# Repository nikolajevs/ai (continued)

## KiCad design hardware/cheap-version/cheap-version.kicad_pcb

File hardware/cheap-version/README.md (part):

# cheap-version — одноразовая плата из того, что есть

Версия **cheap-1** платы GrowBox: те же функции и прошивка, что у PCB_V1 (ревизия 0.22), но детали берутся со склада пользователя, докупается только недостающее. Это отдельный проект, а не ревизия PCB_V1: `../PCB_V1/` не меняется.

**Решения пользователя (03.10.2026):** основа — копия схемы PCB_V1 с заменами; плата 4 слоя, 100×100 мм, стек как у PCB_V1 (1,6 мм, 1 oz снаружи / 0,5 oz внутри); ESP32-WROOM-32E на плате, прошивка и GPIO без изменений; J901 — винтовой клеммник KF301 вместо XT60, защиты от переполюсовки не нужно; L711 — Feryster DTMSS-27/0.047/15-V **на плате стоймя** (корпус будет выше); выходные 10 мкФ 100 В X7S докупаются, как в V1 (4,7 мкФ X7R со склада не берём).

**Решения пользователя (04.10.2026):** CH1 рассчитан на **80 Вт** (R716 0,12 Ом вместо 0,18; LED-панель допускает до 120 Вт, плата её не догружает), драйвер нагревателя — снова **UCC27524ADR** (как в V1) вместо IRS4427S, затем шина +12V и шелкография.

## Состояние

- **Схема готова к проверке** (`cheap-version.kicad_sch` + 6 листов). Её строит `tools/make_cheap1.py` из `../PCB_V1/` (от базовой схемы каждый раз заново). Остальные инструменты: `tools/sch_edit.py` — редактор текста схем, `tools/netdiff.py` — сравнение связности с PCB_V1, `tools/make_footprints.py` — свои футпринты (запуск Python из KiCad), `tools/make_models3d.py` — их 3D-модели (CadQuery), `tools/analyze_led_cheap.py` — расчёт LED-boost. После ручных правок схемы в KiCad `make_cheap1.py` больше не запускать.
- ERC: **0 нарушений**. Связность у всех нетронутых выводов совпадает с PCB_V1 (`netdiff.py`: 0 различий).
- Свои футпринты и упрощённые 3D: `Diodes_PowerDI5`, `L_Feryster_DTMSS-27_V` (`libraries/`). BOM — `BOM_cheap1.csv`, `BUY_cheap1.csv` (см. ниже).
- **Плата `cheap-version.kicad_pcb` разведена, Gerber и сверловка выгружены; перед заказом остаются пункты ([FAB.md](FAB.md)).** 170 деталей, 4 слоя 100×100 мм; 0 пересечений courtyard и выходов за контур; все цепи соединены. ERC 0; DRC (с `.kicad_dru`) 0 нарушений, 0 замечаний, 0 неподключённых; `check_fab.py` 0 FAIL / 2 WARN; `tools/run_checks.py` 9 из 9. Силовая медь входа, PTC, +24V к LED и узлов каналов усилена, линия вентиляторов +12V расширена, добавлен C911 у U902, шелкография очищена (см. ниже). JLCDFM (04.10.2026): единственное правило с Danger — зазор сквозных площадок до SMD-площадок (сборочное, платы не касается), остальное предупреждения, разбор в [FAB.md](FAB.md), раздел 6. Остаются: измерения на макете и корпус.
- Склад: [stock/components-20261003.csv](stock/components-20261003.csv); в схеме поле `Source` = `stock:<id>`, у покупных деталей пусто. Даташиты — [datasheets/](datasheets/README.md) (PDF в git не хранятся).

## Что заменено

| Блок | PCB_V1 | cheap-1 | Склад (id, шт) |
|---|---|---|---|
| 24→12 В (U902) | LMR16020PDDAR | **ST1S14PHR**; R906 (RT) убран | 26: 3 |
| 12→3,3 В (U101) | TPS54202DDCR | **ST1S10PHR**; L101 4,7 мкГн (FXL0630-4R7-M, тот же корпус); R102 31,6 кОм; C103 — не BOOT, а VIN_A (2,2 мкФ) | 27: 4 |
| Нагреватель PTC | UCC27524ADR, NTMFS5C628NL | драйвер **UCC27524ADR как в V1** (ENA на +12V, ENB на GND; было IRS4427S, 04.10.2026), **IRL2505** TO-220 | — (покупается); 78: 1 |
| LED-boost, ключи Q711/Q721 | AOD66923 | **BSC146N10LS5** (TDSON-8-1) | 112: 2 |
| LED-boost, диоды D711/D721 | SS5P10 | **SBRT15U100SP5** (PowerDI5, `GrowBox:Diodes_PowerDI5`) | 8: 5 |
| LED-boost, дроссель L711 | SRP1770TA-470M | **DTMSS-27/0.047/15-V** стоймя (`GrowBox:L_Feryster_DTMSS-27_V`) | 12: 1 |
| Диоды D521, D902 | SS36 | **SS56** (тот же SMC) | 20: 45 |
| Прочая керамика | см. BOM | 10 мкФ 50 В 1210 (C521, C710, C715, C725, C905, C906); 10 мкФ 35 В 1210 (C101, C602, C910); 22 мкФ 10 В 0805 (C104, C105, C401); 2,2 мкФ 16 В 0805 (C103, C203, C302); 10 мкФ 16 В 0805 (C201); 2,2 мкФ 50 В 1206 (C711, C721, C902); 100 нФ 0603 | 47+44; 6; 7; 57; 58; 3; 54 |
| Электролиты | C901 220 мкФ 50 В, C909 100 мкФ полимер | C901 **EEVFK1J471M** 470 мкФ 63 В (Ø16×16,5, футпринт CP_Elec_16x17.5); C909 **EEEFT1E821AP** 820 мкФ 25 В (Ø10) | 13: 1; 14: 1 |
| Резисторы | 0603 | 100 кОм/1 кОм 1 % 0603 (id 55, 62); 10 кОм, 4,7 кОм 0805 (id 70, 59, 72); 10 Ом и 47 кОм 1206 (id 41, 61) | см. CSV |
| Разъёмы | XT60PW-M, DORABO 3,5, KANGNEX 5,08, JST XH, TS-1187A | J901, J711/J721/J731: KF301-5,0-2P (MKDS-1,5-2 5,0); J302/J521/J601: FS1.5-02 3,5 мм; J501/J511: KF2510 4P (Molex KK-254); J301: XH угловой; SW201/SW202: тактовые 6×6×10 | 93; 86; 87; 90; 95 |

Остаётся как в V1 и докупается: UCC27524ADR (C185857, минимум 5 шт), шунт R716 0,12 Ом 2512 (FRM252WFR120TM той же серии, что был 0,18 Ом; номер на LCSC проверить), 7× Murata GRM32EC72A106KE05L (10 мкФ 100 В X7S, выходы LED), ESP32-WROOM-32E, PCF8563T и кварц, 2× AL8853S-13, microSD и держатель CR2032, TVS SMBJ26CA, предохранители и держатель F902, SOT-23 MOSFET, ESD-диоды, дроссели L721 и L902 и FXL0630-4R7-M, шунты, точные и мелкие резисторы и конденсаторы.

## Расчёты и проверка по даташитам

**ST1S14 (24→12 В).** Вход 5,5–48 В, VFB 1,222 В (1,202–1,239), предел тока 3,7–5,2 А, 850 кГц, BOOT 100 нФ, EN1 активный низкий (на GND), EN2 активный высокий (выше 1,5 В), PG не используется. Делитель R904 88,7 кОм 0,1 % + R905 10 кОм 0,1 %: 12,06 В, диапазон 11,9–12,2 В. L902 22 мкГн: пульсация 0,29–0,33 А, пик при 2 А — 2,17 А. EN2 через R907 470 кОм / R908 47 кОм: 1,96 В при 21,6 В, включение гарантировано от 16,5 В. Выходной электролит 820 мкФ (ESR 60 мОм): нуль 3,2 кГц, пульсация около 20 мВ; даташит допускает такие конденсаторы (fZ < BW < fSW/5), устойчивость проверить на макете.

**ST1S10 (12→3,3 В, DocID13844 Rev 7).** Выводы: 1 VIN_A, 2 INH (активный высокий; к VIN_A, если не нужен), 3 VFB, 4 AGND, 5 SYNC (на GND — 900 кГц), 6 VIN_SW, 7 SW, 8 PGND, EP — земля; вход до 18 В, VFB 0,8 В (0,784–0,816), предел тока 5 А, синхронный, диода нет. Делитель 100 кОм / 31,6 кОм: 3,33 В (3,26–3,40 В). Ток при бюджете 1 А: D = 0,28, пульсация 0,59 А на L 4,7 мкГн (диапазон даташита 0,6–1,2 А для 3 А), пик 1,3 А. Даташит проектирует контур под L 3,3 мкГн и C 22 мкФ (18,7 кГц); у cheap-1 L 4,7 мкГн и около 40 мкФ эффективных (3×22 мкФ 10 В): 11,6 кГц, нужна проверка реакции на скачок нагрузки. На входе по рекомендации для выходной ёмкости 47–100 мкФ: VIN_SW 10 мкФ (C101) и VIN_A 2,2 мкФ (C103). Потери около 0,37 Вт, нагрев около 15 К.

**Нагреватель.** Драйвер UCC27524ADR, как в PCB_V1 (IRS4427S убран 04.10.2026: его вход «1» от 2,5 В при минимуме 2,64 В у ESP32 давал запас всего 0,14 В). Выводы: 1 ENA (на +12V; в V1 на +3V3, но рядом нет места под переходное, даташит допускает неиспользуемый ENx на VDD, и внутренняя подтяжка к VDD всё равно держит канал включённым), 2 INA (HEATER_EN), 3 GND, 4 INB (GND), 5 OUTB (не подключён), 6 VDD (+12V), 7 OUTA (HEATER_DRIVE), 8 ENB (GND, канал B выключен). Входы по даташиту не зависят от VDD и рассчитаны на логику 3,3 В; затвор держит R602 100 кОм. IRL2505 при 4,2 А (100 Вт / 24 В): около 0,14 Вт без радиатора; 55 В выше ограничения входной TVS 42 В.

**LED-boost** (`tools/analyze_led_cheap.py`, результат — [review/LED_power_cheap1.txt](review/LED_power_cheap1.txt); модель PCB_V1, заменены только дроссель CH1, диоды и ключи). Все проверки модели проходят. **CH1 на 80 Вт** (R716 0,12 Ом, ток панели до 1,73 А с допусками): ток входа до 4,61 А, пик дросселя до 6,26 А (V1 при 53 Вт — 5,18 А; DTMSS держит 15 А), запас до OCP 2,06 А (R715 остаётся 0,027 Ом: окно OCP 8,3…14,1 А не выше точки 15 А дросселя), RMS дросселя 4,7 А, потери в диоде до 0,96 Вт, в обмотке 0,32 Вт без сердечника, субгармоники 0,18; консервативная оценка пульсации выхода 2,4 Vpp (при 53 Вт 1,6). Потолок канала на этом контроллере и дросселе: около 96 Вт (R716 0,10 Ом, запас OCP 1,13 А); при 120 Вт (R716 0,08 Ом) пик 8,57 А выше нижней границы OCP 8,32 А, канал начнёт упираться в ограничение — поэтому панель на 120 Вт подключается, но работает на 80 Вт. Предохранитель F711 (6,3 А, около 73 % от максимума входного тока) остаётся. CH2 без изменений (запас 0,97 А); выходная ёмкость как в V1. DTMSS-27 (даташит Feryster): 45,5 мкГн при 1 А, около 42 мкГн при 5 А, 26,1 мкГн при 15 А, RDC 10 мОм; в расчёте L = 47 мкГн −20 % и ещё −12 % на пике. BSC146N10LS5: RDS(on) 12,2 мОм типично, 14,6 мОм максимум при 10 В (у AOD66923 11 мОм); Qg 7,6 нКл, Qgd 2,8 нКл (3,5 нКл у AOD66923); выводы S1–S3, G4, D5–8, как в символе.

## Плата: как получено размещение

```sh
python tools/make_cheap1.py                                     # схема
kicad-cli sch export netlist --format kicadxml -o netlist.xml cheap-version.kicad_sch
"C:/Program Files/KiCad/10.0/bin/python.exe" tools/make_board.py netlist.xml      # плата из PCB_V1 без меди, футпринты заменены на месте
"C:/Program Files/KiCad/10.0/bin/python.exe" tools/auto_place.py --steps 80000 --seed 4 --write
"C:/Program Files/KiCad/10.0/bin/python.exe" tools/placement_report.py            # пересечения courtyard и выход за контур
```

`make_board.py` переносит позиции PCB_V1 (55 заменённых футпринтов остаются на своих местах), убирает R906 и обновляет цепи. `auto_place.py` — отжиг по габаритам courtyard (Python из KiCad только читает и пишет плату): энергия = длина цепей (HPWL, без GND) + штраф за смещение от позиции V1 и за поворот + штраф за пересечение и выход за контур. Закреплены ESP32, разъёмы, батарейный держатель, контрольные точки; вручную заданы дроссель L711 (70,9; 120,0; пады на 62,15 и 79,65 мм), J901 вплотную к левому краю (56,3; 62,0) и шунт R716 между клеммами J711 и J721 (Kelvin-метка NT712 едет с ним). Из пяти запусков (seed 1–4 легальны, длина цепей 2433–2465 мм) взят seed 4. Результат — стартовая точка, а не окончательное решение: перед трассировкой плату стоит просмотреть в KiCad; шёлк и подписи не причёсаны.

## Трассировка: состояние (03.10.2026)

**Все цепи соединены:** 1012 дорожек, 231 переходное отверстие; заливки GND на F.Cu/In1.Cu/B.Cu и +3V3 на In2.Cu, пять дополнительных полигонов входа и нагревателя. [Текущий вид F.Cu](review/Routing_top.png). Размещение и назначения выводов сохранены.

Завершены земля, +3V3, AUX_VIN, затворы LED, возврат LED1, питание помпы и измерительное ответвление LED2_OUT. LED2_OVP переложена для доступа к R727. Возврат LED1 приходит на силовой вывод шунта R716, а не на Kelvin net-tie. Отвод к F521 выполнен шириной 1 мм на внешнем слое (расчётный запас помпы 0,5 А); 0,25 мм к R727 — только измерительная ветвь OVP, не питание светильников. Основные силовые пути этими ответвлениями не заменены.

**Проверки:** KiCad 10.0.5: ERC 0; DRC 0 неподключённых цепей, 0 нарушений зазоров/замыканий, 0 замечаний по шелкографии (после `fix_silk.py`; до него было 120: 57 пересечений, 48 над открытой медью, 15 у края). 170 компонентов и 445 электрических выводов соответствуют схеме (`tools/check_sync.py`); размещение без пересечений. `hardware/check_all.py` проходит для основной PCB_V1; эта проверка сама по себе не проверяет cheap-version.

**Исправление инструментов:** `route_power.py`, `route_signals.py`, `route_complete.py` загружают соответствующий `.kicad_pro` вместе с платой. Без него заливка через Python игнорировала зазоры классов: вместо 0,4–0,5 мм применялось 0,2 мм. Доводчик теперь учитывает зазоры обеих цепей, не снимает препятствия возле конечных площадок и не подставляет 0,25 мм для неизвестного силового соединения. Силовые и переключающие цепи пропускает для ручной работы; исключения — только указанные одиночные ответвления F521 и R727. Последующая проверка CLI DRC обязательна.

**Усиление входа и PTC:** между J901 и F902 добавлена медь на F.Cu/B.Cu; +24V_LOADS от F902 к J601 перенесена с In2 на B.Cu. Сток Q601 связан с J601 полигонами на обоих внешних слоях. Площадки силовых THT подключены без терморазгрузки, возле истока Q601 добавлены четыре переходных отверстия Ø0,8/0,4 мм. Ответвление помпы переложено в обход полигона стока. Q601 остаётся вертикальным; размещение, схема и назначения выводов не менялись.

`tools/reinforce_input.py <board> --write` повторяемо обновляет только этот этап, сохраняя остальную трассировку. После него запускать `tools/verify_input_copper.py <board>` и CLI DRC. Проверка использует **фактически залитые** полигоны и контролирует непрерывные участки: вход — минимум 5,95 мм на каждом внешнем слое, питание нагревателя — 5,39 мм на B.Cu, путь стока — 1,75 мм на каждом внешнем слое. Это геометрическая проверка выбранных участков, а не тепловая квалификация всей платы: контактные сужения, металлизация отверстий и распределение тока между слоями требуют итоговой проверки. Остальные силовые цепи описаны ниже.

**Усиление +24V к LED и узлов каналов (04.10.2026):** кольцо +24V на In2 0,5 oz (95 мм, 2 мм) от F902 к F711/F721 и участок LED2_OUT на In2 (0,8 мм, 43 мм) убраны; вместо них внешние слои:

| Участок | Медь | Непрерывная ширина |
|---|---|---|
| +24V через полосу +24V_LOADS | входной полигон F.Cu продолжен под вершину полосы (кромка полосы: y = 157 − x), 10 переходных Ø0,8/0,4 вдоль неё | 7,2 мм до переходных |
| магистраль к CH1 и CH2 | B.Cu, полигон x 71–81,6, y 80–110 | 3,6 мм на самом узком месте |
| ветка к CH2 | B.Cu, полоса y 100–105,6 до F721 | 2,6 мм |
| питание F711 (CH1) | F.Cu, полигон 25×6 мм вместо полосы 2 мм, 12 переходных | 5,2 мм |
| питание F721 (CH2) | F.Cu, полигон + 6 переходных | 4,6 мм |
| LED1_VIN / LED2_VIN | F.Cu, полигоны вместо дорожек 2 мм | 2,2–2,9 мм |
| LED1_SW / LED2_SW | F.Cu, полигоны вместо дорожек 1,5 мм | 4,0–5,0 мм |
| LED2_OUT | B.Cu, 1,2 мм вместо In2 0,8 мм (около 45 мм) | 1,09 мм |

Оценка по IPC-2221 (1 oz, внешний слой): магистраль 3,6 мм при максимуме расчёта (CH1 на 80 Вт 4,61 А + CH2 1,29 А = 5,9 А) даёт около +9 К, полигоны LED1_VIN шириной 2,2 мм при 4,6 А около +12 К на коротком участке. Не менялись: LED1_OUT (0,8 мм на F.Cu, достаточно для 1,67 А), истоки Q711/Q721 (1,5 мм), возвраты, шина +12V.

`tools/reinforce_led.py <board> --write` повторяемо перестраивает только этот этап (зоны `auto:led-stage:*`, нужные дорожки и переходные; ставить после `reinforce_input.py`). `tools/verify_led_copper.py <board.json>` (JSON из `export_view.py`; Python с numpy, scipy и Pillow) считает по залитой меди ширину самого широкого непрерывного пути между точками и число переходных; `tools/freespace.py` — вспомогательный поиск свободных коридоров при проектировании. Результат: `verify_led_copper.py` PASS, DRC (с `.kicad_dru`) 0 ошибок и 0 неподключённых.

**Шина +12V, шелкография, драйвер (04.10.2026):**

- `tools/reinforce_12v.py`: линия вентиляторов (0,68 А) шла по In2 шириной 0,5 мм около 45 мм (около +28 К по IPC-2221); сегменты вне тесного места расширены до 0,8 мм (около +11 К), 6,5-мм перемычка между двумя переходными и дорожкой ESP_IO0 остаётся 0,5 мм (рядом на внешних слоях места нет). Шире B.Cu не получается: коридоры 0,3–0,7 мм.
- `tools/swap_heater_driver.py`: U601 = UCC27524ADR (ENA на +12V короткой перемычкой к рядом идущей дорожке, ENB на GND), значение и MPN у R716 и U601 на плате; схема и плата сверены по всем выводам (расхождений нет), ERC 0.
- `tools/fix_silk.py` (+ `silk_model.py`): удалены 29 линий шелка, которые пересекали площадки или контур платы (корпуса J301, J302, J601, J521 за краем, оси L711 через площадки, перекрытие контуров C901/D901); **все 170 обозначений теперь на шёлке** (168 на F.Silkscreen, 2 на B.Silkscreen — C911 и держатель батарейки), 1,0 мм высотой и штрихом 0,2 мм. До 04.10 только 67 лежали на шёлке, а 103 — на слое F.Fab/B.Fab с высотой 0,8 мм: в KiCad они «видны», но в Gerber шёлка их нет. Проверка геометрическая, штрих против штриха, как в DRC (`silk_model.py`): зазор до шелка 0,18 мм, до площадки 0,17 мм, до отверстий и переходных 0,2 мм, до края 0,45 мм. Медиана расстояния обозначения от выводов своей детали 0,6 мм; в плотных местах 39 обозначений стоят дальше 2 мм (до 10 мм: NT721, TP301, R905, C304, R403, NT712, R307, C103, D303, R410) — там обозначение читается по соседству, а не вплотную. Повторный запуск ничего не меняет. Вид сверху: [review/Board_top_cheap1.png](review/Board_top_cheap1.png).

**Петли DC/DC, пути возврата, производство (04.10.2026, ветка `cheap-fab`):**

- **ST1S14.** Цепь AUX_VIN от входных конденсаторов C905/C906 до вывода VIN 7 была около 20 мм с двумя переходными, половина на B.Cu над потолком +3V3, а не над землёй: оценка петли 13 нГн (`tools/analyze_dcdc_loops.py`, формулы микрополоски над плоскостью и переходного, порядок величины, не моделирование). Добавлен **C911** (100 нФ 0603 со склада, снизу под выводами 6/7, переходное на землю рядом, второе AUX_VIN-переходное у вывода 7; `tools/add_c911.py`): петля 4,8 нГн, выброс на VIN при токе 3,7 А за 5 нс оценивается в 3,5 В над 25 В. Остальные петли в норме: ST1S10 4,4 нГн (C101 в 6,5 мм), boost CH1 и CH2 — диод → выходные конденсаторы 3,7 и 3,8 нГн, SW-узел 1,2 и 1,3 нГн, исток → шунт 1,3 и 0,9 нГн; вся коммутационная петля boost 15–16 нГн (в ней 7 нГн — возврат по In1 от C716/C726 к шунтам R715/R725, 22–24 мм), выброс на SW около 6,5 В (CH1) и 3 В (CH2) при 100-вольтовых ключах и диодах. Устойчивость контуров ST1S14/ST1S10 расчётом не проверена (внутренняя компенсация, модели нет): [review/Bench_checklist_cheap1.md](review/Bench_checklist_cheap1.md).
- **Земля и пути возврата** (`tools/check_return_paths.py`, по заливке): In1 — один кусок меди, 92 % платы, без островов; пустоты больше 8 мм² — зона антенны ESP32 (48 × 6 мм, так задумано), антиконтактные отверстия THT и две «щели» от массивов переходных (8 × 3 мм у питания F711, 6 × 5 мм у перехода +24V; в них нет сигнальных цепей). Самое узкое место земли от входной клеммы J901.1 до силовых каскадов: 7,9–8,5 мм для LED-шунтов и возвратов, 7,2 мм для истока нагревателя, 5,9 мм для U902, 5,5 мм для ESP32 (нужно ≥ 5 мм; 12 А по 8 мм 0,5 oz даёт около 8 мОм, плюс заливки F.Cu и B.Cu). Переключающие цепи над пустотой In1: AUX_VIN 2,2 мм (у переходных рядом с U902), остальные не дольше 3 мм; сигнальные переходные на B.Cu без земляного рядом (11 штук: медленные SD_CS, RTC_VBAT, FAN_TACH, затвор LED1 через 3,4 мм на B.Cu) — информация, не отказ.
- **Производство** — [FAB.md](FAB.md): Gerber и сверловка 12 файлов (`tools/export_fab_cheap.py`), `check_fab.py` 0 FAIL / 2 WARN (как у PCB_V1), исправления по нему (`tools/fab_touchups.py`, `fix_silk.py`). Всё одной командой — `tools/run_checks.py` (9 шагов, около 7 минут): 9 из 9. Загрузка в JLCDFM остаётся за вами.
- **Для оператора сборки** — [assembly/Assembly_cheap1.pdf](assembly/Assembly_cheap1.pdf), 34 страницы A4 на русском: правила, страница «Главное о полярности», 10 шагов сборки (общий план платы с отмеченными деталями, таблица деталей по номиналам с корпусом, MPN и источником), 16 «плоскостей» A1–D4 (по 25 × 25 мм, у каждой детали позиция и номинал, красные метки полярности и вывода 1), карточки полярности и ориентации по типам деталей, контроль после сборки. Не ставятся: контрольные точки TP, пары NT и C106 (DNP). Пересборка после изменения платы: `tools/export_assembly.py` (KiCad Python) → `tools/make_assembly_doc.py` (Python с Pillow и PyMuPDF, шрифт Arial из Windows).
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
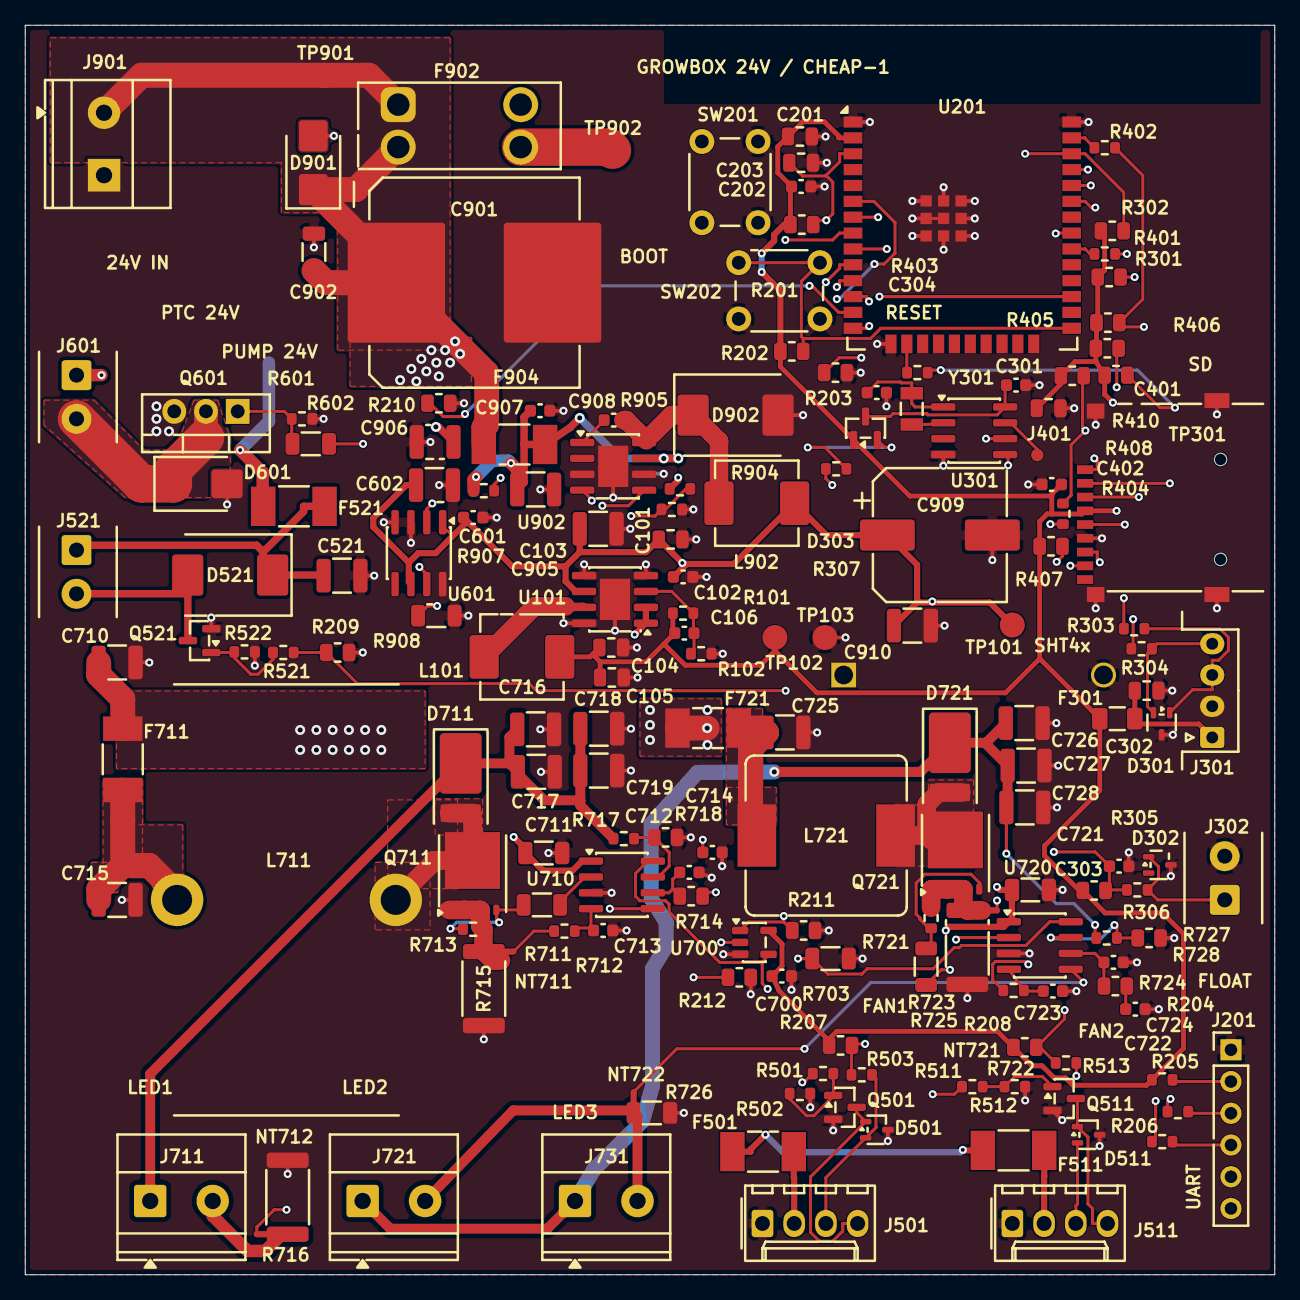
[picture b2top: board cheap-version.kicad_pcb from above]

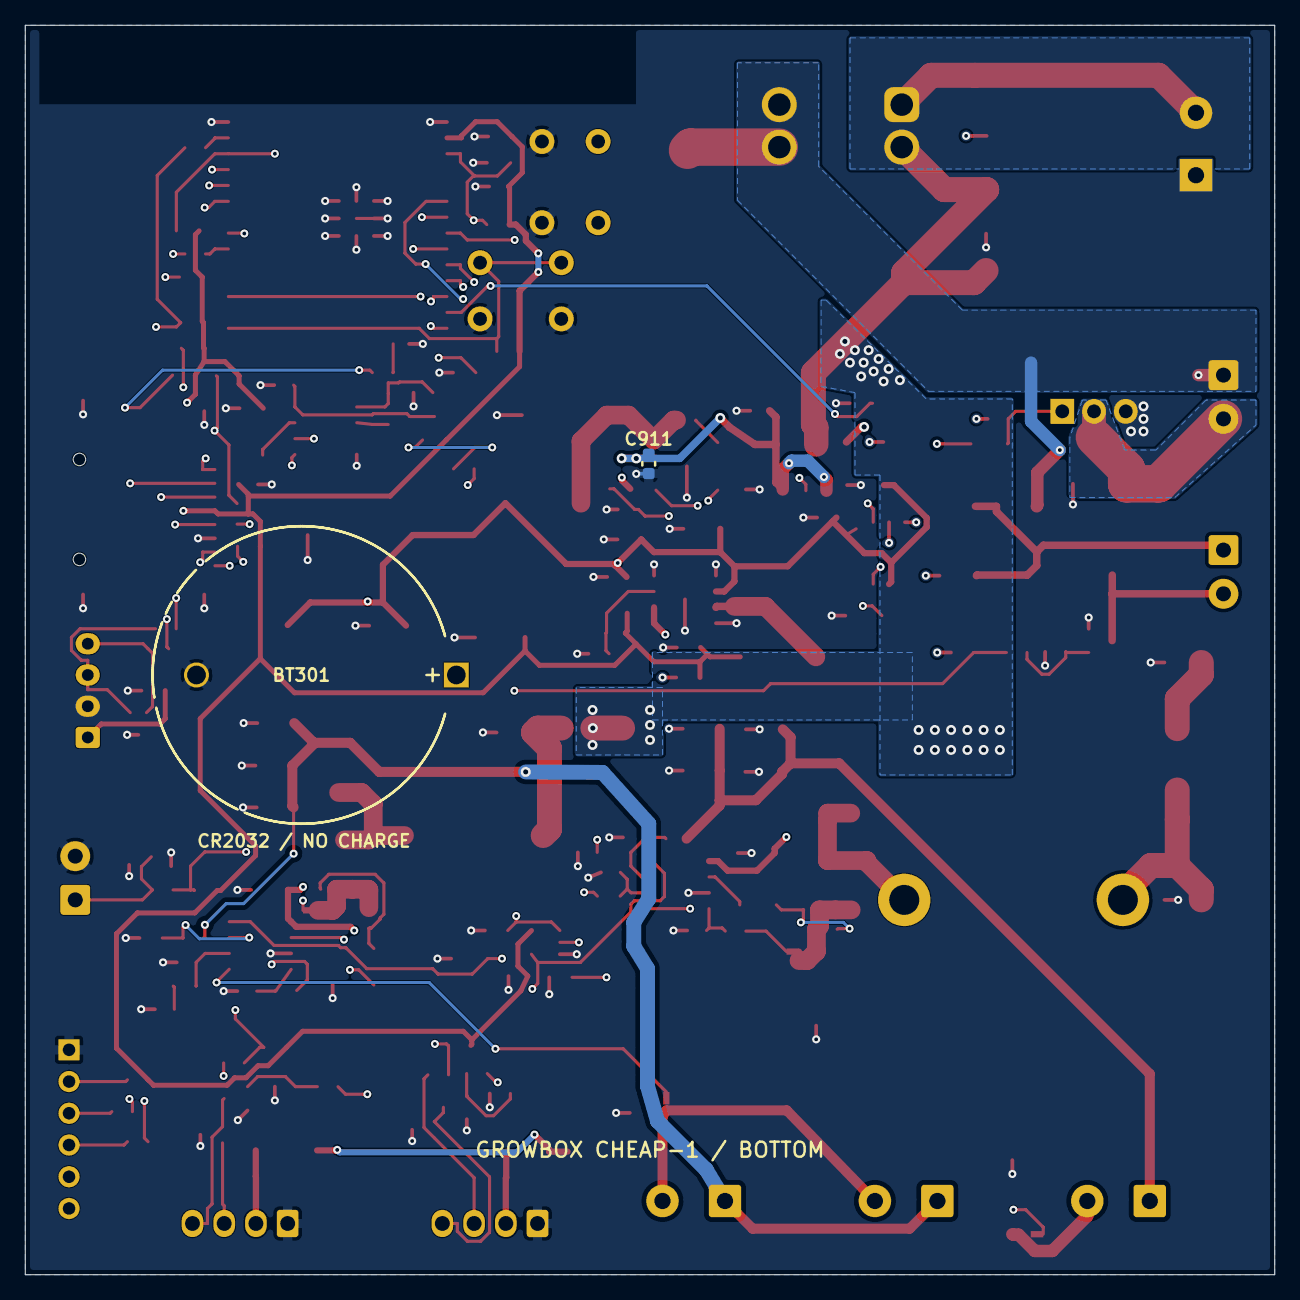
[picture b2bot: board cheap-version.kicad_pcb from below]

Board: 4 copper layers, 100.0 x 100.0 mm, 170 parts (2 on the bottom side), 92 nets.

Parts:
BT301: CR2032 / NO CHARGE; BatteryHolder_MYOUNG_BS-07-A1BJ001_CR2032
C101, C602, C910: 10u 35V X5R; C_1210_3225Metric
C102, C202, C301, C303, C402, C601, C700, C907, C908, C911: 100n 50V X7R; C_0603_1608Metric
C103, C203, C302: 2.2u 16V X5R; C_0805_2012Metric
C104, C105, C401: 22u / 10V X5R; C_0805_2012Metric
C106: 100p / DNP - tune; C_0603_1608Metric
C201: 10u 16V X5R; C_0805_2012Metric
C304: 18p 50V C0G; C_0603_1608Metric
C521: 10u / 50V X7R; C_1210_3225Metric
C710, C715, C725, C905, C906: 10u 50V X7R; C_1210_3225Metric
C711, C721, C902: 2.2u 50V X7R; C_1206_3216Metric
C712, C722: 100p / comp tune; C_0603_1608Metric
C713, C723: 100p / CS tune; C_0603_1608Metric
C714, C724: 220n / comp tune; C_0603_1608Metric
C716, C717, C718, C719, C726, C727, C728: 10u 100V X7S; C_1210_3225Metric
C901: 470u / 63V; CP_Elec_16x17.5
C909: 820u 25V; CP_Elec_10x10.5
D301, D302, D501, D511: TPD2E2U06DCKR; SOT-323_SC-70
D303: BAV170; SOT-23
D521, D902: SS56; D_SMC
D601, D901: SMBJ26CA-E3/52; D_SMB
D711, D721: SBRT15U100SP5; Diodes_PowerDI5
F301: PTC 0.10A / >=16V; Fuse_1206_3216Metric
F501, F511, F521: 1A / 0451001.MRL; Fuse_Littelfuse_451
F711: 6.3A / 045106.3MRL; Fuse_Littelfuse_451
F721, F904: 3A / 0451003.MRL; Fuse_Littelfuse_451
F902: 10A mini blade (ATM); Fuseholder_Blade_Mini_XFCN_XF-508P
J201: UART / 3V3 logic; PinHeader_1x06_P2.54mm_Vertical
J301: SHT4x / XH 2.50; JST_XH_S4B-XH-A_1x04_P2.50mm_Horizontal
J302: FLOAT / 3.5 mm; TerminalBlock_Phoenix_PT-1,5-2-3.5-H_1x02_P3.50mm_Horizontal
J401: HRO TF-01A; microSD_HRO_TF-01A
J501: FAN1 / 3.5 mm; Molex_KK-254_AE-6410-04A_1x04_P2.54mm_Vertical
J511: FAN2 / 3.5 mm; Molex_KK-254_AE-6410-04A_1x04_P2.54mm_Vertical
J521: PUMP 24V / 6W; TerminalBlock_Phoenix_PT-1,5-2-3.5-H_1x02_P3.50mm_Horizontal
J601: PTC + / switched - (3.5 mm); TerminalBlock_Phoenix_PT-1,5-2-3.5-H_1x02_P3.50mm_Horizontal
J711, J721, J731: LED +/- (return isolated); TerminalBlock_Phoenix_MKDS-1,5-2_1x02_P5.00mm_Horizontal
J901: 24V IN (KF301-5.0-2P); TerminalBlock_KF301_1x02_P5.00mm_Horizontal_Input
L101: 4.7u FXL0630-4R7-M; L_Changjiang_FXL0630
L711: 47u DTMSS-27/0.047/15-V; L_Feryster_DTMSS-27_V
L721: 47u SRP1265A-470M; L_Bourns_SRP1265A
L902: 22u PSPMAA0604-220M; L_Changjiang_FXL0630
NT711, NT712, NT721, NT722: Kelvin; NetTie-2_SMD_Pad0.5mm
Q501, Q511: AO3400A; SOT-23
Q521: AO3422; SOT-23
Q601: IRL2505; TO-220-3_Vertical
Q711, Q721: BSC146N10LS5; TDSON-8-1
R101, R502, R512, R522, R602, R713, R723: 100k 1%; R_0603_1608Metric
R102: 31.6k 1%; R_0603_1608Metric
R201, R202, R203, R207, R208, R209, R210, R211, R212, R306, R405, R406, R407, R408, R410, R714, R724: 10k 5%; R_0805_2012Metric
R204, R205, R206, R305, R307, R503, R513, R712: 1k 1%; R_0603_1608Metric
R301, R302: 4.7k 5%; R_0805_2012Metric
R303, R304, R401, R402, R403, R404, R501, R511, R521: 33; R_0603_1608Metric
R601, R711, R721: 10R 5%; R_1206_3216Metric
R703, R908: 47k 1%; R_1206_3216Metric
R715: 0.027 1% >=1W; R_2512_6332Metric
R716: 0.12 1% 3W 50ppm; R_2512_6332Metric
R717, R727: 316k 1%; R_0603_1608Metric
R718, R728: 10k 1%; R_0805_2012Metric
R722: 2.7k 1% / slope tune; R_0603_1608Metric
R725: 0.047 1% >=1W; R_2512_6332Metric
R726: 0.43 1% >=0.25W; R_1206_3216Metric
R904: 88.7k 0.1%; R_0603_1608Metric
R905: 10k 0.1%; R_0603_1608Metric
R907: 470k 1%; R_0603_1608Metric
SW201: RESET; SW_PUSH_6mm_H9.5mm
SW202: BOOT; SW_PUSH_6mm_H9.5mm
TP101: +12V; TestPoint_Pad_D2.0mm
TP102: +3V3; TestPoint_Pad_D2.0mm
TP103: GND; TestPoint_Pad_D2.0mm
TP301: CLKOUT; TestPoint_Pad_D1.0mm
TP901: +24V; TestPoint_Pad_D2.0mm
TP902: +24V_LOADS; TestPoint_Pad_D2.0mm
U101: ST1S10PHR; SOIC-8-1EP_3.9x4.9mm_P1.27mm_EP2.41x3.3mm
U201: ESP32-WROOM-32E-N4; ESP32-WROOM-32E_NoVias
U301: PCF8563T/5; SOIC-8_3.9x4.9mm_P1.27mm
U601: UCC27524ADR; SOIC-8_3.9x4.9mm_P1.27mm
U700: SN74LVC1G08DBVR; SOT-23-5
U710, U720: AL8853S-13; SOIC-8_3.9x4.9mm_P1.27mm
U902: ST1S14PHR; SOIC-8-1EP_3.9x4.9mm_P1.27mm_EP2.41x3.3mm
Y301: 32.768k 12.5pF; Crystal_SMD_3215-2Pin_3.2x1.5mm

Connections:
+3V3: C104.1, C105.1, C106.1, C201.1, C202.1, C401.1, C402.1, C700.1, D303.1, F301.1, J401.4, L101.2, R101.1, R201.1, R202.1, R204.1, R207.1, R208.1, R301.1, R302.1, R306.1, R405.1, R406.1, R407.1, R408.1, R410.1, TP102.1 (1_1), U201.2, U700.5 (VCC)
+12V: C101.1, C102.1, C103.1, C601.1, C602.1, C711.1, C721.1, C909.1, C910.1, F501.1, F511.1, L902.2, R904.1, TP101.1 (1_1), U101.1, U101.2, U101.6, U601.1 (ENA), U601.6 (V_{DD}), U710.1 (VIN), U720.1 (VIN)
+24V: C710.1, C901.1, C902.1, D901.1 (A1), F711.1, F721.1, F902.1, F904.1, J901.2, TP901.1 (1_1)
+24V_LOADS: F521.1, F902.2, J601.1, TP902.1 (1_1)
/BUCK_FB: C106.2, R101.2, R102.1, U101.3
/BUCK_SW: L101.1, U101.7
/InputPower/AUX_VIN: C905.1, C906.1, C907.1, C911.1, F904.2, R907.1, U902.7
/InputPower/BUCK12_BOOT: C908.1, U902.1
/InputPower/BUCK12_EN: R907.2, R908.1, U902.5
/InputPower/BUCK12_FB: R904.2, R905.1, U902.4
/InputPower/BUCK12_SW: C908.2, D902.1, L902.1, U902.8
/LEDDrivers/LED1_COMP: C712.1, R714.1, U710.6 (COMP)
/LEDDrivers/LED1_COMP_RC: C714.1, R714.2
/LEDDrivers/LED1_CS: C713.1, R712.2, U710.4 (CS)
/LEDDrivers/LED1_CS_K: NT711.2, R712.1
/LEDDrivers/LED1_DRV: R711.1, U710.2 (GATE)
/LEDDrivers/LED1_FB_K: NT712.2, U710.5 (FB)
/LEDDrivers/LED1_GATE: Q711.4, R711.2, R713.1
/LEDDrivers/LED1_OUT: C716.1, C717.1, C718.1, C719.1, D711.1, J711.1, R717.1
/LEDDrivers/LED1_OVP: R717.2, R718.1, U710.7 (OVP)
/LEDDrivers/LED1_RETURN: J711.2, NT712.1, R716.1
/LEDDrivers/LED1_SOURCE: NT711.1, Q711.1, Q711.2, Q711.3, R713.2, R715.1
/LEDDrivers/LED1_SW: D711.2, L711.2, Q711.5
/LEDDrivers/LED1_VIN: C715.1, F711.2, L711.1
/LEDDrivers/LED2_COMP: C722.1, R724.1, U720.6 (COMP)
/LEDDrivers/LED2_COMP_RC: C724.1, R724.2
/LEDDrivers/LED2_CS: C723.1, R722.2, U720.4 (CS)
/LEDDrivers/LED2_CS_K: NT721.2, R722.1
/LEDDrivers/LED2_DRV: R721.1, U720.2 (GATE)
/LEDDrivers/LED2_FB_K: NT722.2, U720.5 (FB)
/LEDDrivers/LED2_GATE: Q721.4, R721.2, R723.1
/LEDDrivers/LED2_OUT: C726.1, C727.1, C728.1, D721.1, J721.1, J731.1, R727.1
/LEDDrivers/LED2_OVP: R727.2, R728.1, U720.7 (OVP)
/LEDDrivers/LED2_RETURN: J721.2, J731.2, NT722.1, R726.1
/LEDDrivers/LED2_SOURCE: NT721.1, Q721.1, Q721.2, Q721.3, R723.2, R725.1
/LEDDrivers/LED2_SW: D721.2, L721.2, Q721.5
/LEDDrivers/LED2_VIN: C725.1, F721.2, L721.1
/LEDDrivers/LED_DIM: R703.1, U700.4, U710.8 (PWM), U720.8 (PWM)
/MCU / ESP32/BOOT_VDD_SDIO: R203.1, U201.14
/MCU / ESP32/ESP_EN: C203.1, J201.5, R201.2, SW201.1, U201.3
/MCU / ESP32/ESP_IO0: J201.6, R202.2, SW202.1, U201.25
/MCU / ESP32/PROG_RX_TO_ESP: J201.4, R206.1
/MCU / ESP32/PROG_TX_FROM_ESP: J201.3, R205.2
/MCU / ESP32/Peripherals/RTC_CLKOUT: TP301.1, U301.7 (SDA)
/MCU / ESP32/Peripherals/RTC_OSCI: C304.1, U301.1 (32kHz), Y301.1
/MCU / ESP32/Peripherals/RTC_OSCO: U301.2 (VCC), Y301.2
/MCU / ESP32/Peripherals/RTC_VBAT: BT301.1, R307.1
/MCU / ESP32/Peripherals/RTC_VBAT_R: D303.2, R307.2
/MCU / ESP32/Peripherals/RTC_VDD: C301.1, D303.3, U301.8 (SCL)
/MCU / ESP32/Peripherals/SD_CS_CARD: J401.2, R403.2, R408.2
/MCU / ESP32/Peripherals/SD_DAT1: J401.8, R406.2
/MCU / ESP32/Peripherals/SD_DAT2: J401.1, R407.2
/MCU / ESP32/Peripherals/SD_MISO_CARD: J401.7, R404.2, R405.2
/MCU / ESP32/Peripherals/SD_MOSI_CARD: J401.3, R402.2, R410.2
/MCU / ESP32/Peripherals/SD_SCK_CARD: J401.5, R401.2
/MCU / ESP32/Peripherals/SHT_3V3: C302.1, F301.2, J301.1
/MCU / ESP32/Peripherals/SHT_SCL_EXT: D301.2, J301.4, R304.2
/MCU / ESP32/Peripherals/SHT_SDA_EXT: D301.1, J301.3, R303.2
/MCU / ESP32/Peripherals/WATER_EXT: D302.1, J302.1, R305.2
/MCU / ESP32/UART_RX0: R206.2, U201.34
/MCU / ESP32/UART_TX0: R205.1, U201.35
/MCU / ESP32/VREF_3V3: J201.2, R204.2
/Outputs/FAN1_12V: F501.2, J501.2
/Outputs/FAN1_GATE: Q501.1 (G), R501.2, R502.1
/Outputs/FAN1_PWM_EXT: D501.1, J501.4, Q501.3 (D)
/Outputs/FAN1_TACH_EXT: D501.2, J501.3, R503.2
/Outputs/FAN2_12V: F511.2, J511.2
/Outputs/FAN2_GATE: Q511.1 (G), R511.2, R512.1
/Outputs/FAN2_PWM_EXT: D511.1, J511.4, Q511.3 (D)
/Outputs/FAN2_TACH_EXT: D511.2, J511.3, R513.2
/Outputs/Heater/HEATER_DRAIN: D601.1 (K), J601.2, Q601.2
/Outputs/Heater/HEATER_DRIVE: R601.1, U601.7 (OUTA)
/Outputs/Heater/HEATER_GATE: Q601.1, R601.2, R602.1
/Outputs/PUMP_24V: C521.1, D521.1 (K), F521.2, J521.1
/Outputs/PUMP_DRAIN: D521.2 (A), J521.2, Q521.3 (D)
/Outputs/PUMP_GATE: Q521.1 (G), R521.2, R522.1
FAN1_PWM: R501.1, U201.10
FAN1_TACH: R207.2, R503.1, U201.6
FAN2_PWM: R511.1, U201.11
FAN2_TACH: R208.2, R513.1, U201.7
GND: BT301.2, C101.2, C102.2, C103.2, C104.2, C105.2, C201.2, C202.2, C203.2, C301.2, C302.2, C303.2, C304.2, C401.2, C402.2, C521.2, C601.2, C602.2, C700.2, C710.2, C711.2, C712.2, C713.2, C714.2, C715.2, C716.2, C717.2, C718.2, C719.2, C721.2, C722.2, C723.2, C724.2, C725.2, C726.2, C727.2, C728.2, C901.2, C902.2, C905.2, C906.2, C907.2, C909.2, C910.2, C911.2, D301.3, D302.3, D501.3, D511.3, D601.2 (A), D901.2 (A2), D902.2, J201.1, J301.2, J302.2, J401.6, J401.SH, J501.1, J511.1, J901.1, Q501.2 (S), Q511.2 (S), Q521.2 (S), Q601.3, R102.2, R203.2, R209.2, R210.2, R211.2, R212.2, R502.2, R512.2, R522.2, R602.2, R703.2, R715.2, R716.2, R718.2, R725.2, R726.2, R728.2, R905.2, R908.2, SW201.2, SW202.2, TP103.1 (1_1), U101.4, U101.5, U101.8, U101.9, U201.1, U201.15, U201.38, U201.39, U301.4 (~RST), U601.3 (GND), U601.4 (INB), U601.8 (ENB), U700.3 (GND), U710.3 (GND), U720.3 (GND), U902.3, U902.6, U902.9
HEATER_EN: R210.1, U201.13, U601.2 (INA)
I2C_SCL: R302.2, R304.1, U201.36, U301.6 (VBAT)
I2C_SDA: R301.2, R303.1, U201.33, U301.5 (GND)
LIGHT_ENABLE: R212.1, U201.27, U700.2
LIGHT_PWM: R211.1, U201.8, U700.1
PUMP_EN: R209.1, R521.1, U201.12
SD_CS: R403.1, U201.16
SD_MISO: R404.1, U201.31
SD_MOSI: R402.1, U201.37
SD_SCK: R401.1, U201.30
WATER_LEVEL: C303.1, R305.1, R306.2, U201.9

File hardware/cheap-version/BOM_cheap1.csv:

Line,Designators,Qty,Value,Footprint,Manufacturer,MPN,LCSC,Source,From stock,To buy,Stock note
1,BT301,1,CR2032 / NO CHARGE,BatteryHolder_MYOUNG_BS-07-A1BJ001_CR2032,MYOUNG,BS-07-A1BJ001,C2979167,buy,0,1,
2,BT301,1,CR2032 cell,,,CR2032,,buy,0,1,
3,C101 C602 C910,3,10u 35V X5R,C_1210_3225Metric,Samsung Electro-Mechanics,CL32A106KLULNNE,C2980162,stock:6,3,0,"id 6: 8 in stock, 3 used"
4,C102 C202 C301 C303 C402 C601 C700 C907 C908 C911,10,100n 50V X7R,C_0603_1608Metric,Samsung,CL10B104KB8NNNC,C1591,stock:54,10,0,"id 54: 23 in stock, 10 used"
5,C103 C203 C302,3,2.2u 16V X5R,C_0805_2012Metric,Samsung Electro-Mechanics,CL21A225KOFNNNE,,stock:57,3,0,"id 57: 18 in stock, 3 used"
6,C104 C105 C401,3,22u / 10V X5R,C_0805_2012Metric,Samsung Electro-Mechanics,CL21A226KPCLRNC,C318688,stock:7,3,0,"id 7: 9 in stock, 3 used"
7,C201,1,10u 16V X5R,C_0805_2012Metric,Samsung Electro-Mechanics,CL21A106KAYNNNE,C15850,stock:58,1,0,"id 58: 7 in stock, 1 used"
8,C304,1,18p 50V C0G,C_0603_1608Metric,Samsung,CL10C180JB8NNNC,C1647,buy,0,1,
9,C521,1,10u / 50V X7R,C_1210_3225Metric,Samsung Electro-Mechanics,CL32B106KBJNNNE,C92388,stock:47,1,0,"id 47: 6 in stock, 6 used (no spare)"
10,C710 C715 C725 C905 C906,5,10u 50V X7R,C_1210_3225Metric,Samsung Electro-Mechanics,CL32B106KBJNNNE,C92388,stock:47,5,0,"id 47: 6 in stock, 6 used (no spare)"
11,C711 C721 C902,3,2.2u 50V X7R,C_1206_3216Metric,KYOCERA AVX,12065C225KATM-HW,,stock:3,3,0,"id 3: 9 in stock, 3 used"
12,C712 C713 C722 C723,4,100p,C_0603_1608Metric,Samsung,CL10C101JB8NNNC,C14858,buy,0,4,
13,C714 C724,2,220n,C_0603_1608Metric,Samsung,CL10B224KB8NNNC,C64705,buy,0,2,
14,C716 C717 C718 C719 C726 C727 C728,7,10u 100V X7S,C_1210_3225Metric,Murata,GRM32EC72A106KE05L,C576517,buy,0,7,
15,C901,1,470u / 63V,CP_Elec_16x17.5,Panasonic,EEVFK1J471M,C178728,stock:13,1,0,"id 13: 1 in stock, 1 used (no spare)"
16,C909,1,820u 25V,CP_Elec_10x10.5,Panasonic,EEEFT1E821AP,C178593,stock:14,1,0,"id 14: 1 in stock, 1 used (no spare)"
17,D301 D302 D501 D511,4,TPD2E2U06DCKR,SOT-323_SC-70,TECH PUBLIC,TPD2E2U06DCKR-TP,C5350871,buy,0,4,
18,D303,1,BAV170,SOT-23,JSCJ,BAV170,C68970,buy,0,1,
19,D521 D902,2,SS56,D_SMC,,SS56,,stock:20,2,0,"id 20: 45 in stock, 2 used"
20,D601 D901,2,SMBJ26CA-E3/52,D_SMB,Vishay,SMBJ26CA-E3/52,C515606,buy,0,2,
21,D711 D721,2,SBRT15U100SP5,Diodes_PowerDI5,Diodes Incorporated,SBRT15U100SP5-13,C2934601,stock:8,2,0,"id 8: 5 in stock, 2 used"
22,F301,1,PTC 0.10A / >=16V,Fuse_1206_3216Metric,TECHFUSE,nSMD010,C70065,buy,0,1,
23,F501 F511 F521,3,1A / 0451001.MRL,Fuse_Littelfuse_451,Littelfuse,0451001.MRL,C3099,buy,0,3,
24,F711,1,6.3A / 045106.3MRL,Fuse_Littelfuse_451,Littelfuse,045106.3MRL,C178982,buy,0,1,
25,F721 F904,2,3A / 0451003.MRL,Fuse_Littelfuse_451,Littelfuse,0451003.MRL,C13982,buy,0,2,
26,F902,1,10A mini blade (ATM),Fuseholder_Blade_Mini_XFCN_XF-508P,XFCN,XF-508P-B-B,C19727305,buy,0,1,
27,F902 insert,1,"Littelfuse 0297010.WXNV, 10 A mini blade fuse",,Littelfuse,0297010.WXNV,C151094,buy,0,1,
28,J201,1,UART / 3V3 logic,PinHeader_1x06_P2.54mm_Vertical,BOOMELE,2.54-1x6P,C37208,buy,0,1,
29,J301,1,SHT4x / XH 2.50,JST_XH_S4B-XH-A_1x04_P2.50mm_Horizontal,,XH2.54-4P-90,,stock:90,1,0,"id 90: 60 in stock, 1 used"
30,J302,1,FLOAT / 3.5 mm,"TerminalBlock_Phoenix_PT-1,5-2-3.5-H_1x02_P3.50mm_Horizontal",,FS1.5-02-350-2601R,,stock:86,1,0,"id 86: 7 in stock, 3 used"
31,J401,1,HRO TF-01A,microSD_HRO_TF-01A,Korean Hroparts Elec,TF-01A,C91145,buy,0,1,
32,J501,1,FAN1 / 3.5 mm,Molex_KK-254_AE-6410-04A_1x04_P2.54mm_Vertical,,KF2510-4P,,stock:87,1,0,"id 87: 9 in stock, 2 used"
33,J511,1,FAN2 / 3.5 mm,Molex_KK-254_AE-6410-04A_1x04_P2.54mm_Vertical,,KF2510-4P,,stock:87,1,0,"id 87: 9 in stock, 2 used"
34,J521,1,PUMP 24V / 6W,"TerminalBlock_Phoenix_PT-1,5-2-3.5-H_1x02_P3.50mm_Horizontal",,FS1.5-02-350-2601R,,stock:86,1,0,"id 86: 7 in stock, 3 used"
35,J601,1,PTC + / switched - (3.5 mm),"TerminalBlock_Phoenix_PT-1,5-2-3.5-H_1x02_P3.50mm_Horizontal",,FS1.5-02-350-2601R,,stock:86,1,0,"id 86: 7 in stock, 3 used"
36,J711 J721 J731,3,LED +/- (return isolated),"TerminalBlock_Phoenix_MKDS-1,5-2_1x02_P5.00mm_Horizontal",,KF301-5.0-2P,,stock:93,3,0,"id 93: 31 in stock, 4 used"
37,J901,1,24V IN (KF301-5.0-2P),TerminalBlock_KF301_1x02_P5.00mm_Horizontal_Input,,KF301-5.0-2P,,stock:93,1,0,"id 93: 31 in stock, 4 used"
38,L101,1,4.7u FXL0630-4R7-M,L_Changjiang_FXL0630,cjiang,FXL0630-4R7-M,C167220,buy,0,1,
39,L711,1,47u DTMSS-27/0.047/15-V,L_Feryster_DTMSS-27_V,Feryster,DTMSS-27/0.047/15-V,,stock:12,1,0,"id 12: 1 in stock, 1 used (no spare)"
40,L721,1,47u SRP1265A-470M,L_Bourns_SRP1265A,Bourns,SRP1265A-470M,C840530,buy,0,1,
41,L902,1,22u PSPMAA0604-220M,L_Changjiang_FXL0630,PROD Tech,PSPMAA0604-220M-ANP,C53190553,buy,0,1,
42,Q501 Q511,2,AO3400A,SOT-23,AOS,AO3400A,C20917,buy,0,2,
43,Q521,1,AO3422,SOT-23,AOS,AO3422,C37130,buy,0,1,
44,Q601,1,IRL2505,TO-220-3_Vertical,,IRL2505,,stock:78,1,0,"id 78: 1 in stock, 1 used (no spare)"
45,Q711 Q721,2,BSC146N10LS5,TDSON-8-1,Infineon Technologies,BSC146N10LS5,,stock:112,2,0,"id 112: 2 in stock, 2 used (no spare)"
46,R101 R502 R512 R522 R602 R713 R723,7,100k 1%,R_0603_1608Metric,Yageo,RC0603FR-07100KL,C14675,stock:55,7,0,"id 55: 14 in stock, 7 used"
47,R102,1,31.6k 1%,R_0603_1608Metric,UNI-ROYAL,0603WAF3162T5E,C25967,buy,0,1,
48,R201 R202 R203 R207 R208 R209 R210 R211 R212 R306 R405 R406 R407 R408 R410 R714 R724,17,10k 5%,R_0805_2012Metric,UNI-ROYAL,0603WAF1002T5E,C25804,stock:70,17,0,"id 70: 85 in stock, 17 used"
49,R204 R205 R206 R305 R307 R503 R513 R712,8,1k 1%,R_0603_1608Metric,Yageo,RC0603FR-071KL,C21190,stock:62,8,0,"id 62: 14 in stock, 8 used"
50,R301 R302,2,4.7k 5%,R_0805_2012Metric,UNI-ROYAL,0603WAF4701T5E,C23162,stock:72,2,0,"id 72: 85 in stock, 2 used"
51,R303 R304 R401 R402 R403 R404 R501 R511 R521,9,33,R_0603_1608Metric,UNI-ROYAL,0603WAF330JT5E,C23140,buy,0,9,
52,R601 R711 R721,3,10R 5%,R_1206_3216Metric,UNI-ROYAL,0603WAF100JT5E,C22859,stock:41,3,0,"id 41: 5 in stock, 3 used"
53,R703 R908,2,47k 1%,R_1206_3216Metric,Yageo,RC0603FR-0747KL,C105579,stock:61,2,0,"id 61: 6 in stock, 2 used"
54,R715,1,0.027 1% >=1W,R_2512_6332Metric,UNI-ROYAL,LR123WF270MT4E,C19633795,buy,0,1,
55,R716,1,0.12 1% 3W 50ppm,R_2512_6332Metric,JIERR,JER2512F3R120,C49164917,buy,0,1,
56,R717 R727,2,316k 1%,R_0603_1608Metric,UNI-ROYAL,0603WAF3163T5E,C25814,buy,0,2,
57,R718 R728,2,10k 1%,R_0805_2012Metric,UNI-ROYAL,0603WAF1002T5E,C25804,stock:59,2,0,"id 59: 19 in stock, 2 used"
58,R722,1,2.7k 1%,R_0603_1608Metric,UNI-ROYAL,0603WAF2701T5E,C13167,buy,0,1,
59,R725,1,0.047 1% >=1W,R_2512_6332Metric,RVR,HIXD25NR047F,C52015951,buy,0,1,
60,R726,1,0.43 1% >=0.25W,R_1206_3216Metric,TA-I,RLH12FTCR430,C22464907,buy,0,1,
61,R904,1,88.7k 0.1%,R_0603_1608Metric,Yageo,RT0603BRD0788K7L,C728599,buy,0,1,
62,R905,1,10k 0.1%,R_0603_1608Metric,Yageo,RT0603BRD0710KL,C95204,buy,0,1,
63,R907,1,470k 1%,R_0603_1608Metric,UNI-ROYAL,0603WAF4703T5E,C23178,buy,0,1,
64,SW201,1,RESET,SW_PUSH_6mm_H9.5mm,,6X6X10MM Tact Switch,,stock:95,1,0,"id 95: 15 in stock, 2 used"
65,SW202,1,BOOT,SW_PUSH_6mm_H9.5mm,,6X6X10MM Tact Switch,,stock:95,1,0,"id 95: 15 in stock, 2 used"
66,U101,1,ST1S10PHR,SOIC-8-1EP_3.9x4.9mm_P1.27mm_EP2.41x3.3mm,STMicroelectronics,ST1S10PHR,C11175,stock:27,1,0,"id 27: 4 in stock, 1 used"
67,U201,1,ESP32-WROOM-32E-N4,ESP32-WROOM-32E_NoVias,Espressif,ESP32-WROOM-32E-N4,C701341,buy,0,1,
68,U301,1,PCF8563T/5,SOIC-8_3.9x4.9mm_P1.27mm,NXP,"PCF8563T/5,518",C7440,buy,0,1,
69,U601,1,UCC27524ADR,SOIC-8_3.9x4.9mm_P1.27mm,TI,UCC27524ADR,C185857,buy,0,1,
70,U700,1,SN74LVC1G08DBVR,SOT-23-5,TI,SN74LVC1G08DBVR,C7666,buy,0,1,
71,U710 U720,2,AL8853S-13,SOIC-8_3.9x4.9mm_P1.27mm,Diodes,AL8853S-13,C3192318,buy,0,2,
72,U902,1,ST1S14PHR,SOIC-8-1EP_3.9x4.9mm_P1.27mm_EP2.41x3.3mm,STMicroelectronics,ST1S14PHR,C84130,stock:26,1,0,"id 26: 3 in stock, 1 used"
73,Y301,1,32.768k 12.5pF,Crystal_SMD_3215-2Pin_3.2x1.5mm,Epson,Q13FC13500004,C32346,buy,0,1,

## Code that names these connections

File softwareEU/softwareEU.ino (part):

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// освободило линию, затем сформировать STOP и переинициализировать Wire.
void recoverI2CBus() {
  Wire.end(); // Stop the driver before temporarily taking over its GPIOs.
  pinMode(I2C_SDA_PIN, INPUT_PULLUP);
  pinMode(I2C_SCL_PIN, OUTPUT_OPEN_DRAIN);
  digitalWrite(I2C_SCL_PIN, HIGH);

  if (digitalRead(I2C_SDA_PIN) == HIGH) {
    // Шина уже свободна — восстанавливать нечего, просто переинициализируем Wire
    Wire.begin(I2C_SDA_PIN, I2C_SCL_PIN);
    return;
  }

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
  // До 9 тактов SCL — по спецификации I2C этого достаточно, чтобы slave, зависший
  // в середине передачи байта, дотактовал его до конца и отпустил SDA
  for (int i = 0; i < 9 && digitalRead(I2C_SDA_PIN) == LOW; i++) {
    digitalWrite(I2C_SCL_PIN, LOW);
    delayMicroseconds(5);
    digitalWrite(I2C_SCL_PIN, HIGH);
    delayMicroseconds(5);
  }

  // Формируем STOP-условие вручную (SDA LOW->HIGH, пока SCL HIGH), чтобы сбросить
  // внутренний автомат состояний slave-устройства в исходное состояние
  pinMode(I2C_SDA_PIN, OUTPUT_OPEN_DRAIN);
  digitalWrite(I2C_SDA_PIN, LOW);
  delayMicroseconds(5);
  digitalWrite(I2C_SCL_PIN, HIGH);
  delayMicroseconds(5);
  digitalWrite(I2C_SDA_PIN, HIGH);
  delayMicroseconds(5);

  pinMode(I2C_SDA_PIN, INPUT_PULLUP);
  if (digitalRead(I2C_SDA_PIN) == LOW) {
    logPrintln("[I2C] Восстановить шину не удалось — SDA всё ещё LOW.");
  } else {
    logPrintln("[I2C] Шина восстановлена.");
  }

  Wire.begin(I2C_SDA_PIN, I2C_SCL_PIN);
}

// Читает датчик уровня воды. PCB_EU: внешняя подтяжка 10k к 3,3 В, GPIO14 = INPUT;
// датчик замыкает его на GND, когда вода есть — LOW = "вода в норме", HIGH = "воды нет".
// Если у конкретного датчика логика обратная — поменяй местами LOW/HIGH здесь, в одном месте.
bool isWaterAvailable() {
  return digitalRead(WATER_LEVEL_PIN) == LOW;
}

// --- Диагностика I2C и SHT4x. Всё пишется в веб-консоль, чтобы причину отказа было видно без USB ---
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  pinMode(PUMP_PIN, OUTPUT);
  digitalWrite(PUMP_PIN, LOW);
  // LOW opens each fan's external PWM wire: full airflow throughout setup/reset.
  for (int pin : {FAN1_PWM_PIN, FAN2_PWM_PIN}) {
    gpio_set_level(gpio_num_t(pin), LOW);
    pinMode(pin, OUTPUT);
    digitalWrite(pin, LOW);
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  #endif
  // Explicit channels keep LED timer 0 separate from the 25 kHz fan timer 1.
  if (!ledcAttachChannel(LED_PWM_PIN, LED_PWM_FREQ, PWM_RES, LED_PWM_CHANNEL) ||
      !ledcAttachChannel(FAN1_PWM_PIN, FAN_PWM_FREQ, PWM_RES, FAN1_PWM_CHANNEL) ||
      !ledcAttachChannel(FAN2_PWM_PIN, FAN_PWM_FREQ, PWM_RES, FAN2_PWM_CHANNEL)) {
    for (int pin : {LED_PWM_PIN, FAN1_PWM_PIN, FAN2_PWM_PIN}) {
      ledcDetach(pin);
      pinMode(pin, OUTPUT);
      digitalWrite(pin, LOW);
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    while (true) { esp_task_wdt_reset(); delay(1000); }
  }
  ledcWrite(LED_PWM_PIN, 0);
  ledcWrite(FAN1_PWM_PIN, fanGpioDuty(PWM_MAX));
  ledcWrite(FAN2_PWM_PIN, fanGpioDuty(PWM_MAX));

  Wire.begin(I2C_SDA_PIN, I2C_SCL_PIN);
  delay(300); // Даём I2C-шине и датчикам (SHT4x/RTC) стабилизироваться после подачи питания —
              // без этой паузы begin() может провалиться из-за гонки при старте платы
  recoverI2CBus(); // На случай, если шина осталась "залипшей" ещё с прошлого включения
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  state.last_water_day = last_watering_day;

  state.is_day = true;
  state.fan1_pwm = state.fan2_pwm = PWM_MAX; // Logical airflow; boot GPIO duty is zero.

  // Безопасная инициализация датчиков с проверкой работоспособности.
  // Пробуем несколько раз с паузой — при старте платы I2C-шина/датчик могут быть
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  }
  logI2CScan(); // Одна строка при каждом старте: кто вообще отвечает на шине

  SPI.begin(SD_SCK_PIN, SD_MISO_PIN, SD_MOSI_PIN, SD_CS_PIN);
  if (!SD.begin(SD_CS_PIN, SPI)) logPrintln("SD-карта не обнаружена.");
  if (!SPIFFS.begin(true)) logPrintln("Ошибка SPIFFS!");

  // Датчик уровня воды: внешняя подтяжка 10k; GPIO32 — только выход нагревателя.
  // Если у твоего датчика логика обратная (замыкание = "воды нет") — поменяй LOW на HIGH в isWaterAvailable().
  pinMode(WATER_LEVEL_PIN, INPUT);
  delay(10); // Даём входу установиться: с фильтрующим конденсатором первое чтение иначе ложный LOW
  const bool waterNow = isWaterAvailable();
  water_level = {waterNow, waterNow, (uint32_t)millis()};
  state.water_present = waterNow;

  // GPIO34/35 have no internal pull-ups; the board has 10k pull-ups and 1k series resistors.
  if (!tachBegin(0, FAN1_TACH_PIN)) logPrintln("[Fans] Тахометр вентилятора 1 (PCNT) не запустился.");
  if (!tachBegin(1, FAN2_TACH_PIN)) logPrintln("[Fans] Тахометр вентилятора 2 (PCNT) не запустился.");
  last_tach_ms = millis();

  // AP+STA сразу и навсегда: точка доступа больше не передёргивается задачей телеметрии
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    state.fan2_pwm = target_fan2;

    ledcWrite(LED_PWM_PIN, target_led);
    ledcWrite(FAN1_PWM_PIN, fanGpioDuty(target_fan1));
    ledcWrite(FAN2_PWM_PIN, fanGpioDuty(target_fan2));
  }

  // Запись лога на SD-карту с флагами состояния
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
